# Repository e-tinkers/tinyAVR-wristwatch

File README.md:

## tinyAVR Wrist Watch

This is a derivated design from my entry for [Hackaday 2024 Business Card Challenge Contest](https://hackaday.io/project/196294-business-card-clock-attiny3227-dev-board). 

It shares the same [firmware](https://github.com/e-tinkers/tinyAVR_business_card_firmware) used in the [business card project](https://github.com/e-tinkers/tinyAVR-Business-Card), it has the same BOM with the exception of the two buttons used and without the two 12-pin break-out connector. I found a 16mm-wide wrist belt from Aliexpress and bought a few of them with different colors.

The wrist watch is powered by a CR2016 coin cell battery (96mAh) and has a sleep power consumption of less than 2uA, the battery life would be more than 3 years based on viewing the time 24 times/day.

Thanks [PCBWay](https://www.pcbway.com) for sponsoring the PCB fabrication.

You can ordering your PCB from [PCBWay](https://www.pcbway.com/project/shareproject/W515726AS2D5_gerber_22fd22c4.html)

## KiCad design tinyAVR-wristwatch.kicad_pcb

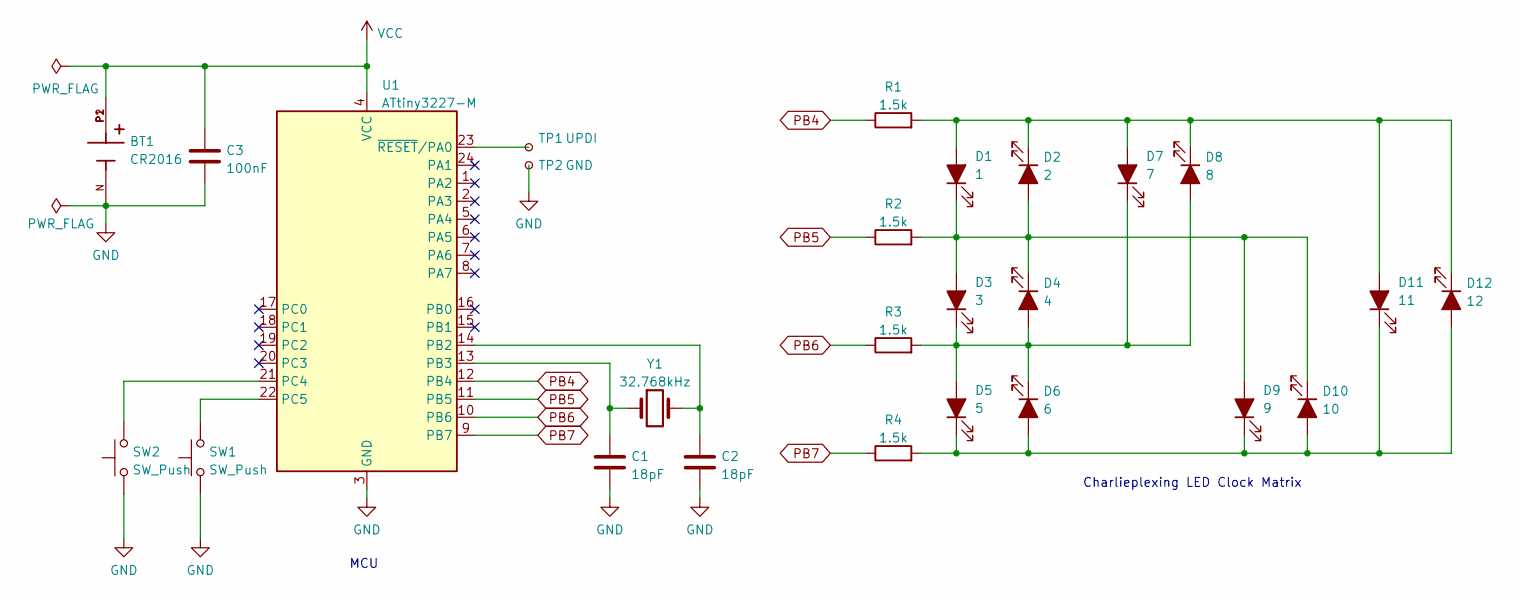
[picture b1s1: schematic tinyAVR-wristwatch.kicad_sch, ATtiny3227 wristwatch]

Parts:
BT1: CR2016; BatteryHolder_CR2016_SMD
C1, C2: 18pF; C_0603_1608Metric
C3: 100nF; C_0603_1608Metric
D1: 1; LED_0603_1608Metric
D2: 2; LED_0603_1608Metric
D3: 3; LED_0603_1608Metric
D4: 4; LED_0603_1608Metric
D5: 5; LED_0603_1608Metric
D6: 6; LED_0603_1608Metric
D7: 7; LED_0603_1608Metric
D8: 8; LED_0603_1608Metric
D9: 9; LED_0603_1608Metric
D10: 10; LED_0603_1608Metric
D11: 11; LED_0603_1608Metric
D12: 12; LED_0603_1608Metric
R1, R2, R3, R4: 1.5k; R_0603_1608Metric
SW1, SW2: SW_Push; KEY-SMD_TS3819ZJ
TP1: UPDI; TestPoint_Pad_D1.5mm
TP2: GND; TestPoint_Pad_D1.5mm
U1: ATtiny3227-M; QFN-24-1EP_4x4mm_P0.5mm_EP2.6x2.6mm
Y1: 32.768kHz; Crystal_SMD_3215-2Pin_3.2x1.5mm

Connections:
GND: BT1.N, C1.2, C2.2, C3.2, SW1.1, SW2.1, TP2.1, U1.3 (GND), U1.25 (GND)
unnamed: C1.1, U1.13 (PB3), Y1.1
unnamed: C2.1, U1.14 (PB2), Y1.2
unnamed: D1.1 (K), D2.2 (A), D3.2 (A), D4.1 (K), D9.2 (A), D10.1 (K), R2.2
unnamed: D1.2 (A), D2.1 (K), D7.2 (A), D8.1 (K), D11.2 (A), D12.1 (K), R1.2
unnamed: D3.1 (K), D4.2 (A), D5.2 (A), D6.1 (K), D7.1 (K), D8.2 (A), R3.2
unnamed: D5.1 (K), D6.2 (A), D9.1 (K), D10.2 (A), D11.1 (K), D12.2 (A), R4.2
unnamed: SW1.2, U1.22 (PC5)
unnamed: SW2.2, U1.21 (PC4)
unnamed: TP1.1, U1.23 (~RESET/PA0)
PB4: R1.1, U1.12 (PB4)
PB5: R2.1, U1.11 (PB5)
PB6: R3.1, U1.10 (PB6)
PB7: R4.1, U1.9 (PB7)
VCC: BT1.P1, BT1.P2, C3.1, U1.4 (VCC)

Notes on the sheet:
MCU
Charlieplexing LED Clock Matrix

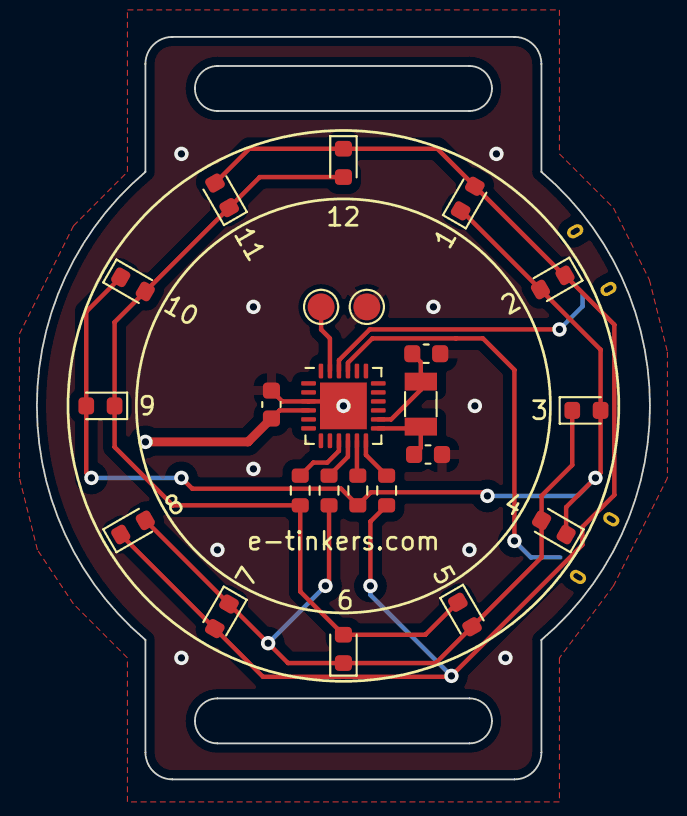
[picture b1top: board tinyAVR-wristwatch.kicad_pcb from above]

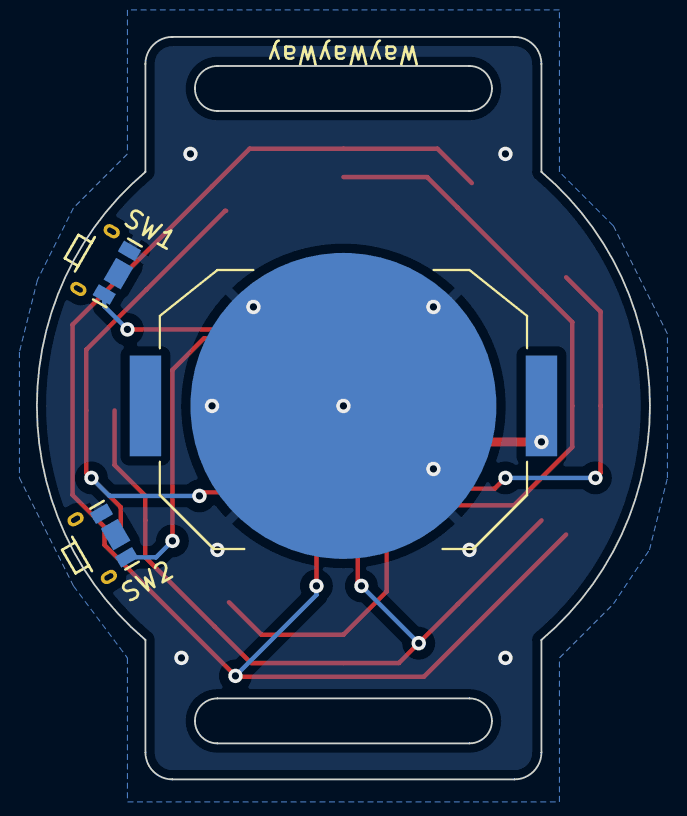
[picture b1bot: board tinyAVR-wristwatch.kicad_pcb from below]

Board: 2 copper layers, 34.1 x 41.2 mm, 26 parts (3 on the bottom side), 15 nets.

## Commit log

2024-06-13 remove gerber files
2024-06-13 add watch image
2024-06-13 add image to README
2024-06-27 add PCB ordering link
